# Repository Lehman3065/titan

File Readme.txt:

https://Lehman3065@bitbucket.org/Lehman3065/titan.git
password: lermontov

https://github.com/Lehman3065/titan.git
password: git9....9

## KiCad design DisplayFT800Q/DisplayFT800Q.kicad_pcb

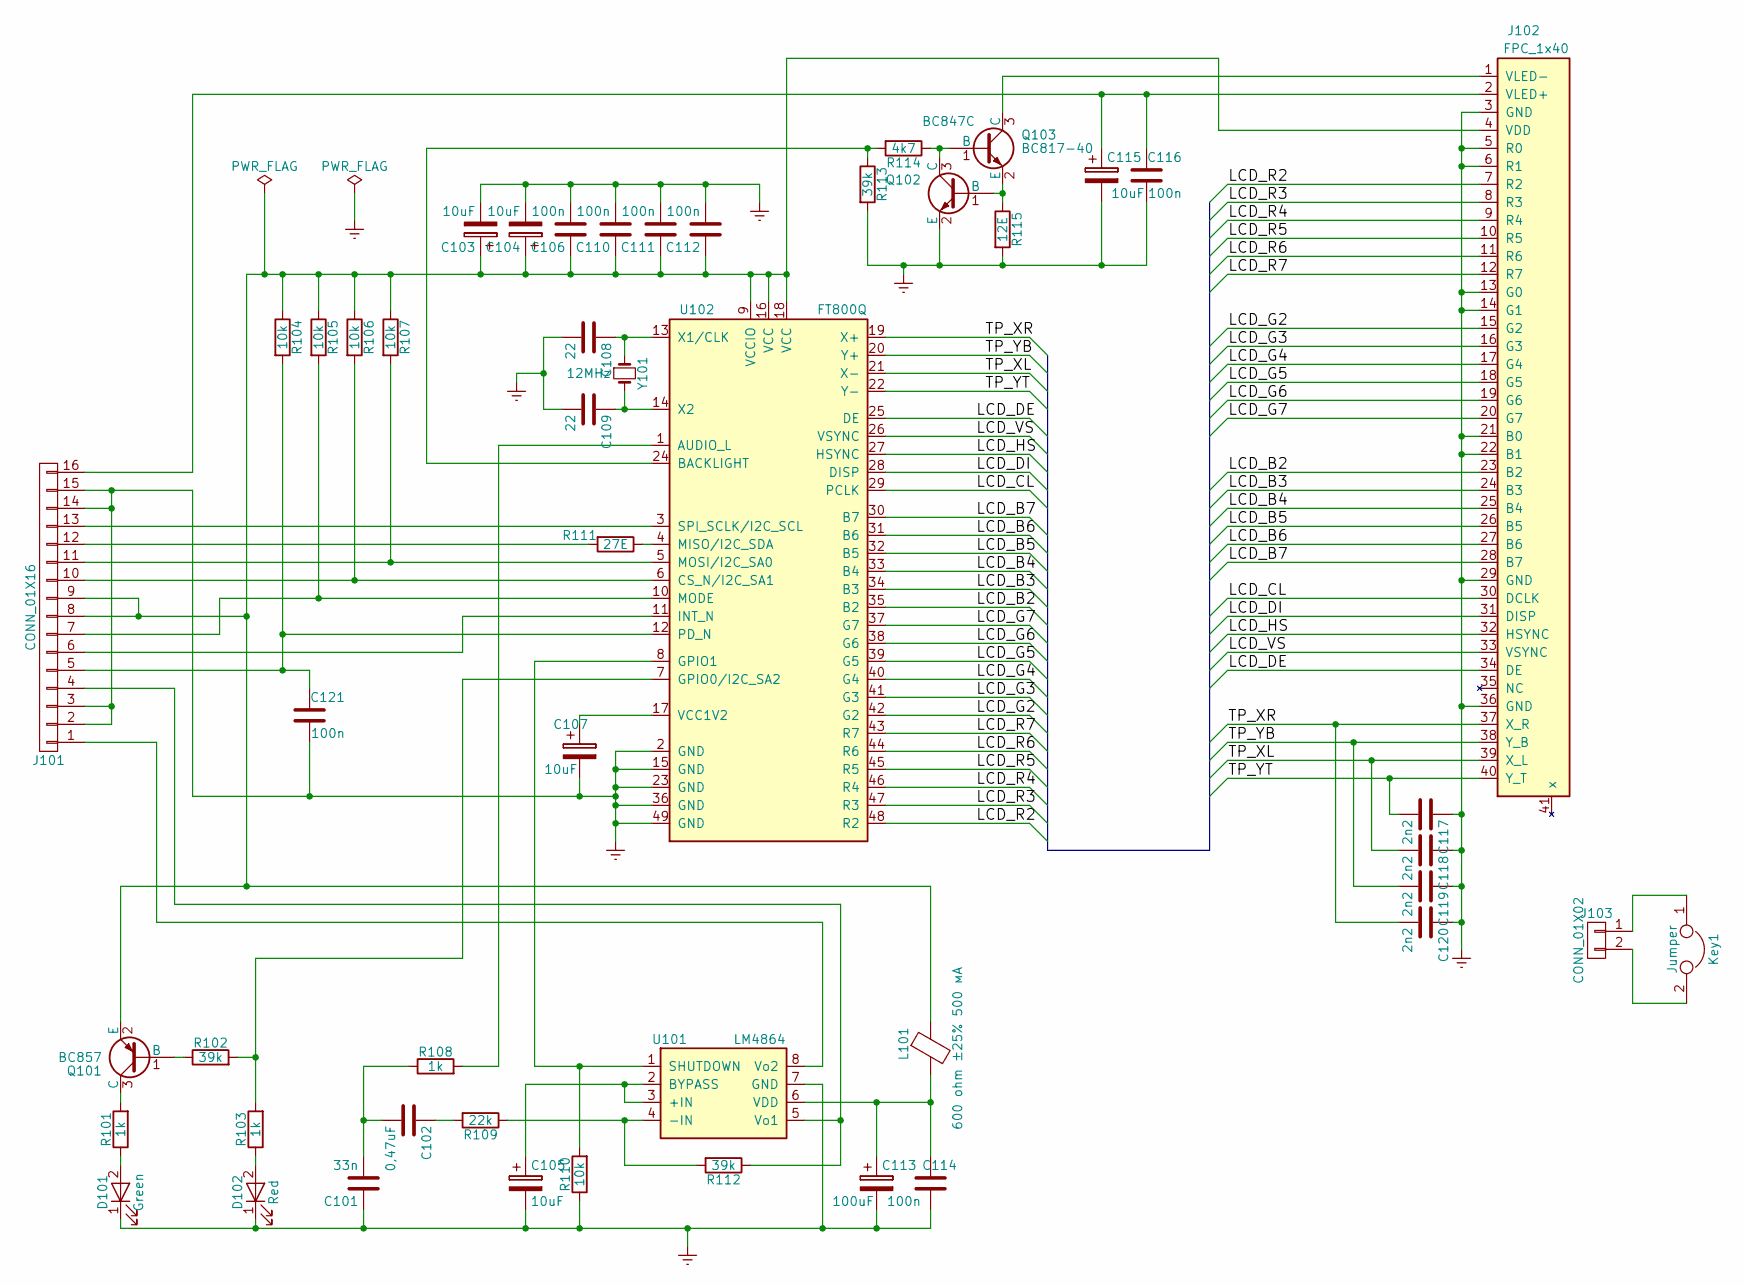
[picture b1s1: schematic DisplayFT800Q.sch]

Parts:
C101: 33n; C_0603
C102: 0,47uF; R_0805
C103, C104, C105, C107, C115: 10uF; C_0805
C106, C110, C111, C112, C114, C116, C121: 100n; C_0603
C108, C109: 22; C_0603
C113: 100uF; CP_Radial_D6.3mm_P2.50mm
C117, C118, C119, C120: 2n2; C_0603
D101: Green; LED_D3.0mm
D102: Red; LED_D3.0mm
J101: CONN_01X16; IDC_DIP_Header_Straight_16pins
J102: FPC_1x40; FPC_1x40_0.5mm
J103: CONN_01X02; TerminalBlock_Pheonix_MKDS1.5-2pol
Key1: Jumper; SW_Tactile_Straight_KSL0Axx1LFTR
L101: 600 ohm ±25% 500 мА; L_0603
Q101: BC857; SOT-23
Q102: BC847C; SOT-23
Q103: BC817-40; SOT-23
R101, R103, R108: 1k; R_0603
R102, R112, R113: 39k; R_0603
R104, R105, R106, R107, R110: 10k; R_0603
R109: 22k; R_0603
R111: 27E; R_0603
R114: 4k7; R_0603
R115: 12E; R_0603
U101: LM4864; TSSOP-8_3x3mm_Pitch0.65mm
U102: FT800Q; QFN-48-1EP_7x7mm_Pitch0.5mm
Y101: 12MHz; Crystal_SMD_HC49-SD

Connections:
/LCD_B2: J102.23 (B2), U102.35 (B2)
/LCD_B3: J102.24 (B3), U102.34 (B3)
/LCD_B4: J102.25 (B4), U102.33 (B4)
/LCD_B5: J102.26 (B5), U102.32 (B5)
/LCD_B6: J102.27 (B6), U102.31 (B6)
/LCD_B7: J102.28 (B7), U102.30 (B7)
/LCD_CL: J102.30 (DCLK), U102.29 (PCLK)
/LCD_DE: J102.34 (DE), U102.25 (DE)
/LCD_DI: J102.31 (DISP), U102.28 (DISP)
/LCD_G2: J102.15 (G2), U102.42 (G2)
/LCD_G3: J102.16 (G3), U102.41 (G3)
/LCD_G4: J102.17 (G4), U102.40 (G4)
/LCD_G5: J102.18 (G5), U102.39 (G5)
/LCD_G6: J102.19 (G6), U102.38 (G6)
/LCD_G7: J102.20 (G7), U102.37 (G7)
/LCD_HS: J102.32 (HSYNC), U102.27 (HSYNC)
/LCD_R2: J102.7 (R2), U102.48 (R2)
/LCD_R3: J102.8 (R3), U102.47 (R3)
/LCD_R4: J102.9 (R4), U102.46 (R4)
/LCD_R5: J102.10 (R5), U102.45 (R5)
/LCD_R6: J102.11 (R6), U102.44 (R6)
/LCD_R7: J102.12 (R7), U102.43 (R7)
/LCD_VS: J102.33 (VSYNC), U102.26 (VSYNC)
/TP_XL: C118.2, J102.39 (X_L), U102.21 (X-)
/TP_XR: C120.2, J102.37 (X_R), U102.19 (X+)
/TP_YB: C119.2, J102.38 (Y_B), U102.20 (Y+)
/TP_YT: C117.2, J102.40 (Y_T), U102.22 (Y-)
Earth: C101.1, C103.2, C104.2, C105.2, C106.2, C107.2, C108.2, C109.2, C110.2, C111.2, C112.2, C113.2, C114.1, C115.2, C116.1, C117.1, C118.1, C119.1, C120.1, C121.1, D101.1 (K), D102.1 (K), J101.2, J101.3, J101.14, J101.15, J102.3 (GND), J102.5 (R0), J102.6 (R1), J102.13 (G0), J102.14 (G1), J102.21 (B0), J102.22 (B1), J102.29 (GND), J102.36 (GND), Q102.2 (E), R110.1, R113.2, R115.2, U101.7 (GND), U102.2 (GND), U102.15 (GND), U102.23 (GND), U102.36 (GND), U102.49 (GND)
unnamed: C101.2, C102.2, R108.1
unnamed: C102.1, R109.2
unnamed: C103.1, C104.1, C106.1, C110.1, C111.1, C112.1, J101.8, J101.9, J102.4 (VDD), L101.1, Q101.2 (E), R104.1, R105.1, R106.1, R107.1, U102.9 (VCCIO), U102.16 (VCC), U102.18 (VCC)
unnamed: C105.1, U101.2 (BYPASS), U101.3 (+IN)
unnamed: C107.1, U102.17 (VCC1V2)
unnamed: C108.1, U102.13 (X1/CLK), Y101.1
unnamed: C109.1, U102.14 (X2), Y101.2
unnamed: C113.1, C114.2, L101.2, U101.6 (VDD)
unnamed: C115.1, C116.2, J101.16, J102.2 (VLED+)
unnamed: D101.2 (A), R101.1
unnamed: D102.2 (A), R103.1
unnamed: J101.1, U101.8 (Vo2)
unnamed: J101.4, R112.1, U101.5 (Vo1)
unnamed: C121.2, J101.5, R104.2, U102.12 (PD_N)
unnamed: J101.6, U102.11 (INT_N)
unnamed: J101.7, R105.2, U102.10 (MODE)
unnamed: J101.10, R106.2, U102.6 (CS_N/I2C_SA1)
unnamed: J101.11, R107.2, U102.5 (MOSI/I2C_SA0)
unnamed: J101.12, R111.2
unnamed: J101.13, U102.3 (SPI_SCLK/I2C_SCL)
unnamed: J102.1 (VLED-), Q103.3 (C)
unnamed: J103.1, Key1.1
unnamed: J103.2, Key1.2
unnamed: Q101.1 (B), R102.1
unnamed: Q101.3 (C), R101.2
unnamed: Q102.1 (B), Q103.2 (E), R115.1
unnamed: Q102.3 (C), Q103.1 (B), R114.1
unnamed: R102.2, R103.2, U102.7 (GPIO0/I2C_SA2)
unnamed: R108.2, U102.1 (AUDIO_L)
unnamed: R109.1, R112.2, U101.4 (-IN)
unnamed: R110.2, U101.1 (SHUTDOWN), U102.8 (GPIO1)
unnamed: R111.1, U102.4 (MISO/I2C_SDA)
unnamed: R113.1, R114.2, U102.24 (BACKLIGHT)

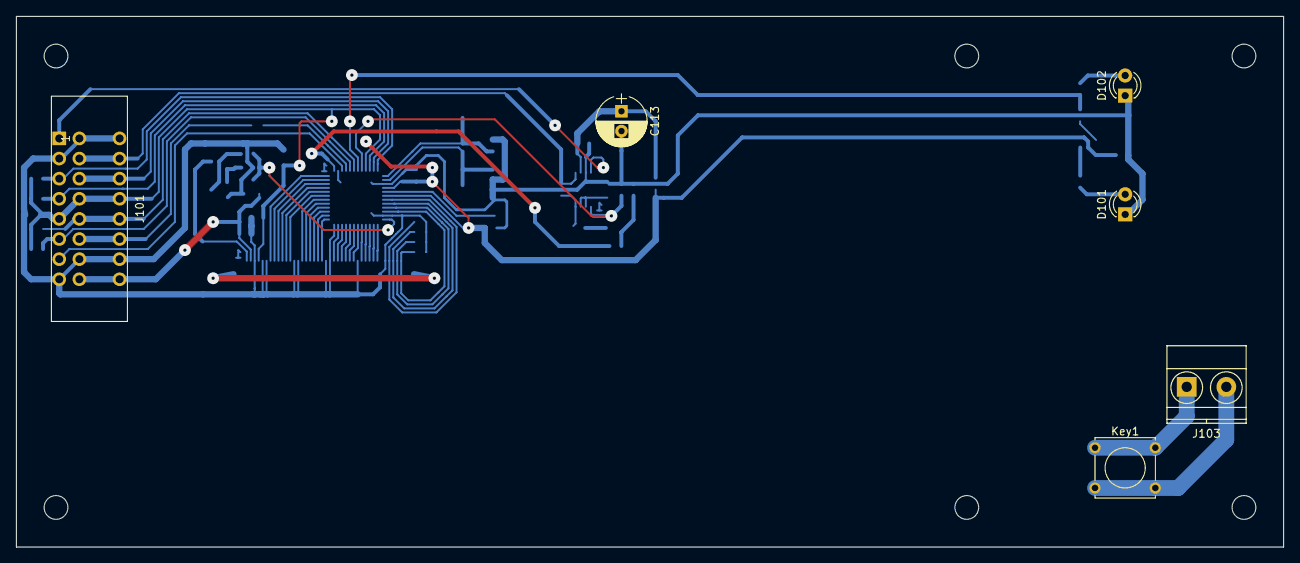
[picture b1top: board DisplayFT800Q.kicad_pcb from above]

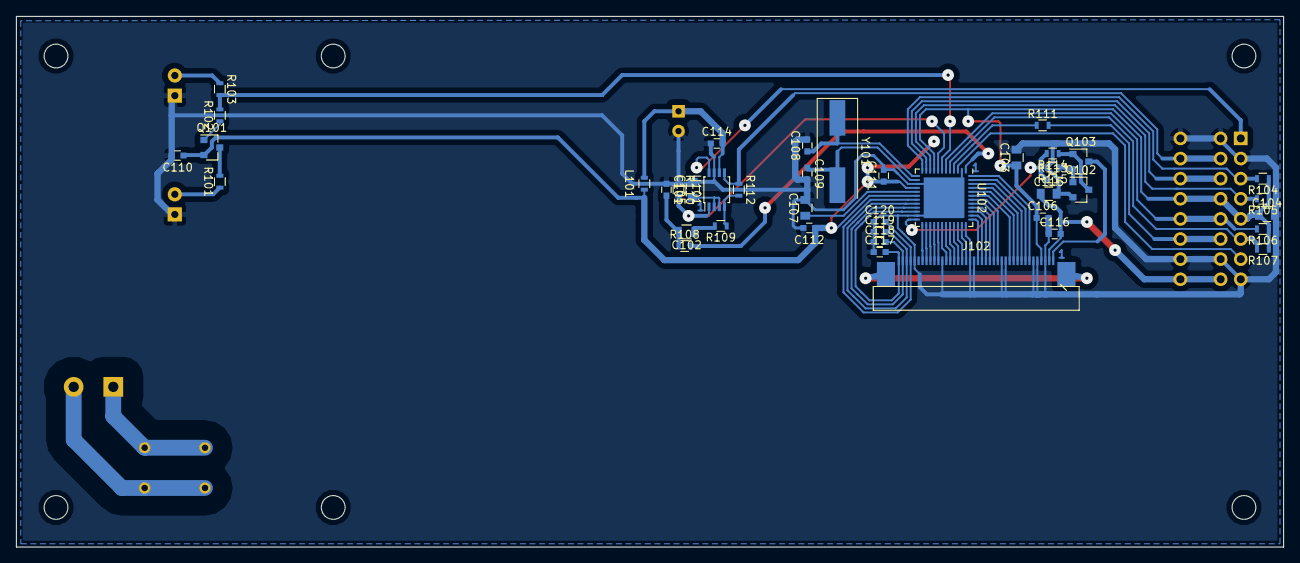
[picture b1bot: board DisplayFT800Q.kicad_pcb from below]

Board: 2 copper layers, 160.0 x 67.0 mm, 48 parts (42 on the bottom side), 61 nets.

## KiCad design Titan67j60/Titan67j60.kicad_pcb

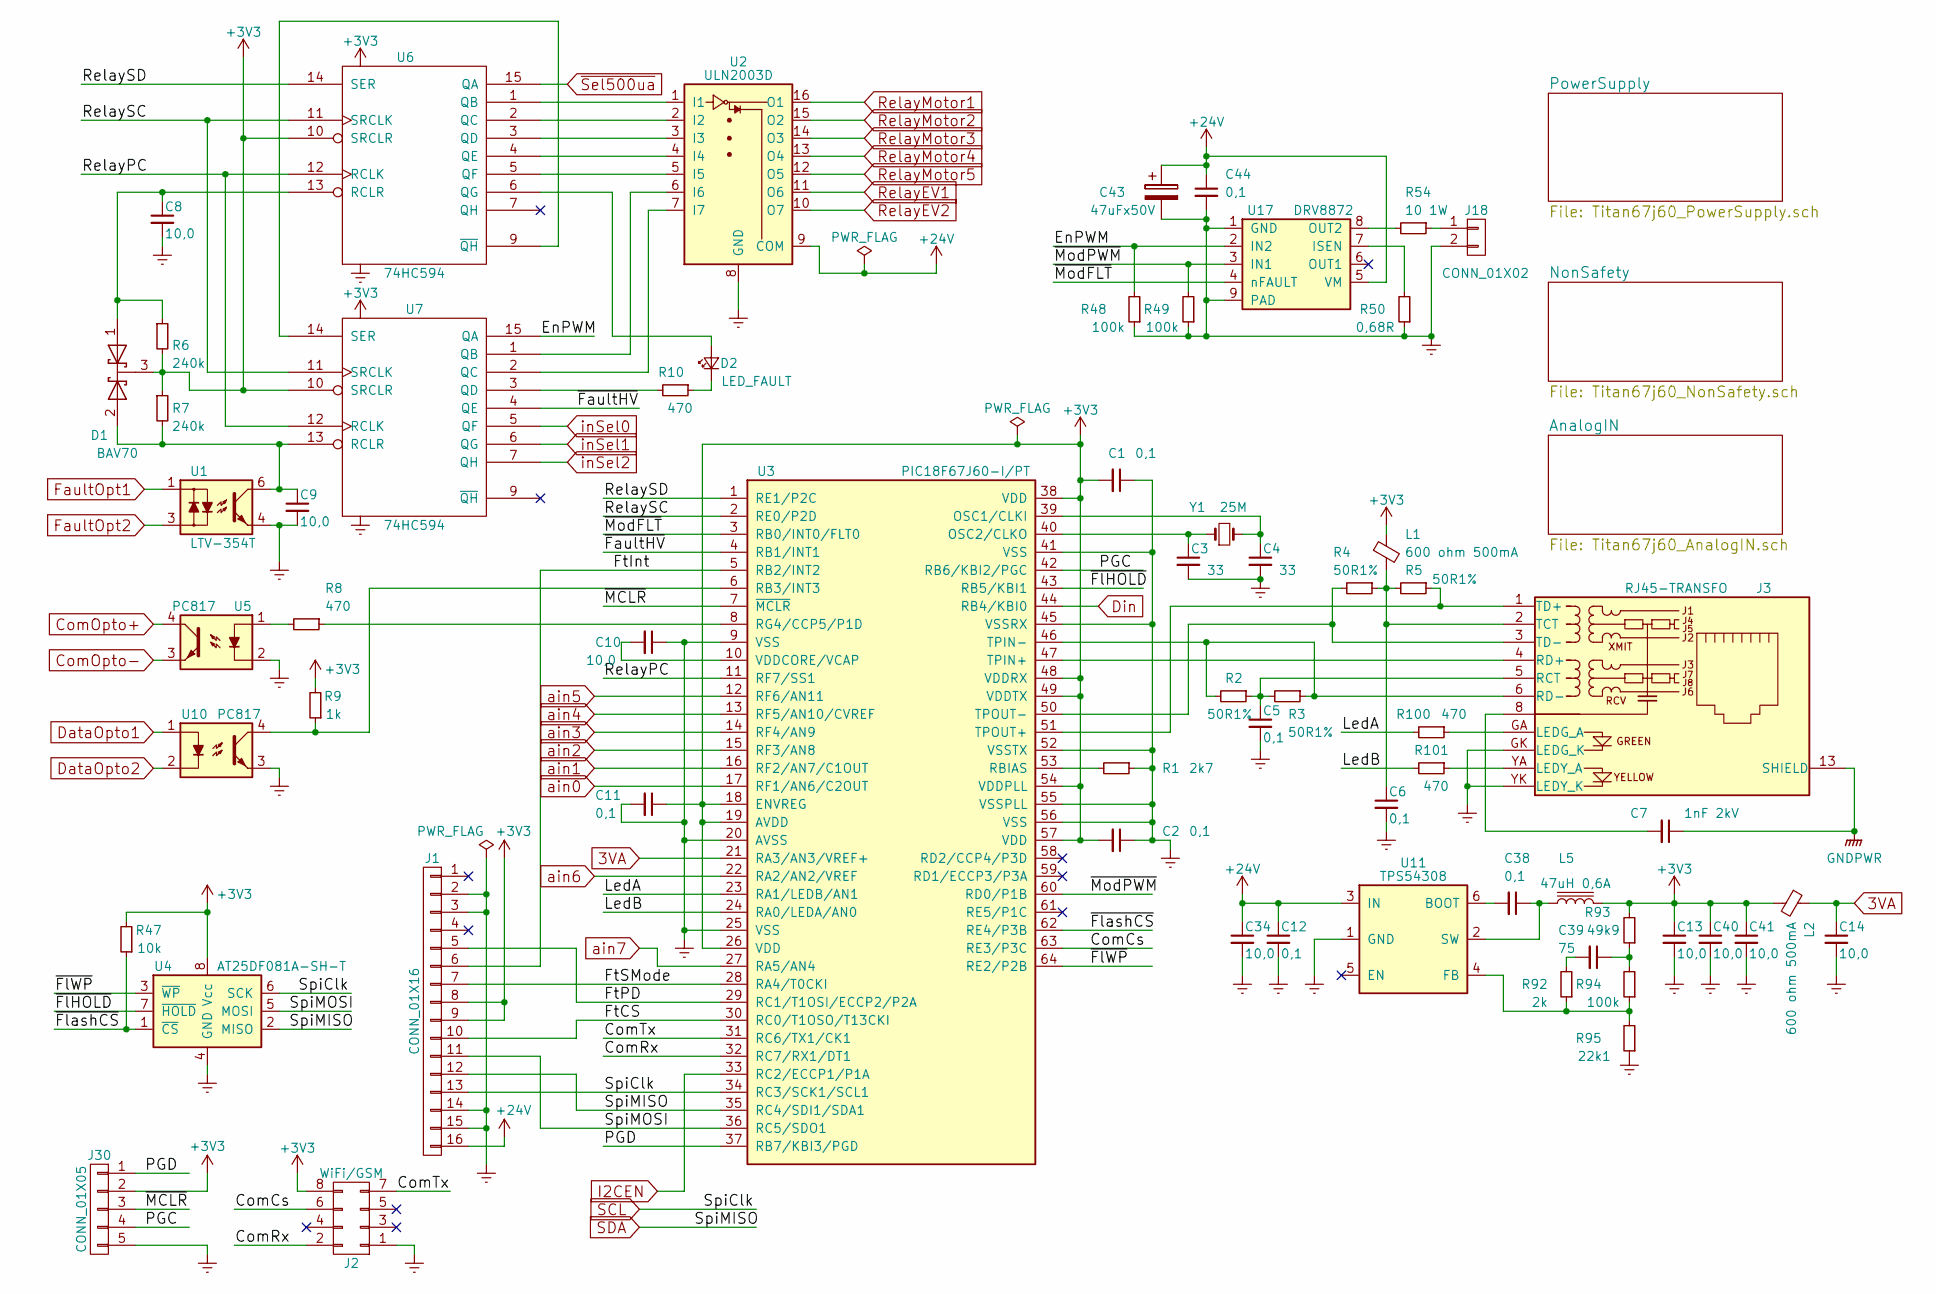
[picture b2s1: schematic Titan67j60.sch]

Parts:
C1, C2, C5, C6, C11, C38, C44: 0,1; C_0603
C3, C4: 33; C_0603
C7: 1nF 2kV; C_Disc_D10.5mm_W5.0mm_P10.00mm
C8, C9, C10, C13, C14, C40, C41: 10,0; C_0805
C12: 0,1; C_0805
C34: 10,0; C_1206
C39: 75; C_0603
C43: 47uFx50V; CP_Radial_D10.0mm_P5.00mm
D1: BAV70; SOT-23
D2: LED_FAULT; LED_D5.0mm
J1: CONN_01X16; Multicomp_MC9A12-1634_2x08x2.54mm_Straight
J2: WiFi/GSM; SDL-108-X-XX_2x04
J3: RJ45-TRANSFO; RJ45_TRANS_J0011D21BNL
J18: CONN_01X02; PhoenixContact_MSTBVA-G_02x5.08mm_Vertical
J30: CONN_01X05; TerminalBlock_Pheonix_MPT-2.54mm_5pol
L1, L2: 600 ohm 500mA; L_0603
L5: 47uH 0,6A; L_Vishay_IHLP-5050
R1: 2k7; R_0603
R2, R3, R4, R5: 50R1%; R_0603
R6, R7: 240k; R_0603
R8, R10, R100, R101: 470; R_0603
R9: 1k; R_0603
R47: 10k; R_0805
R48, R49, R94: 100k; R_0603
R50: 0,68R; R_1210
R54: 10 1W; R_Axial_DIN0414_L11.9mm_D4.5mm_P15.24mm_Horizontal
R92: 2k; R_0603
R93: 49k9; R_0603
R95: 22k1; R_0603
U1: LTV-354T; DIP-6_W7.62mm_SMD
U2: ULN2003D; SOIC-16_3.9x9.9mm_Pitch1.27mm
U3: PIC18F67J60-I/PT; TQFP-64_10x10mm_Pitch0.5mm
U4: AT25DF081A-SH-T; SOIC-8_3.9x4.9mm_Pitch1.27mm
U5, U10: PC817; DIP-4_W7.62mm
U6, U7: 74HC594; SOIC-16_3.9x9.9mm_Pitch1.27mm
U11: TPS54308; SOT-23-6
U17: DRV8872; TI_SO-PowerPAD-8
Y1: 25M; Crystal_SMD_HC49-SD

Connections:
3VA: C14.1, L2.1, U3.21 (RA3/AN3/VREF+); also elsewhere on the board
+3V3: C1.2, C2.2, C11.1, C13.1, C40.1, C41.1, D1.3 (K), J1.8, J1.9, J2.8, J30.2, L1.1, L2.2, L5.2, R6.2, R7.1, R9.2, R47.2, R93.2, U3.18 (ENVREG), U3.19 (AVDD), U3.26 (VDD), U3.38 (VDD), U3.48 (VDDRX), U3.49 (VDDTX), U3.54 (VDDPLL), U3.57 (VDD), U4.8 (Vcc), U6.10 (SRCLR), U6.16 (VCC), U7.10 (SRCLR), U7.16 (VCC); also elsewhere on the board
+24V: C12.1, C34.1, C43.1, C44.1, J1.16, U2.9 (COM), U11.3 (IN), U17.5 (VM); also elsewhere on the board
/ComCs: J2.6, U3.63 (RE3/P3C)
/ComRx: J2.2, U3.32 (RC7/RX1/DT1)
/ComTx: J2.7, U3.31 (RC6/TX1/CK1)
/EnPWM: R48.2, U7.15 (QA), U17.2 (IN2)
/FtCS: J1.10, U3.30 (RC0/T1OSO/T13CKI)
/FtInt: J1.6, U3.5 (RB2/INT2)
/FtPD: J1.5, U3.29 (RC1/T1OSI/ECCP2/P2A)
/FtSMode: J1.7, U3.28 (RA4/T0CKI)
/LedA: R100.2, U3.23 (RA1/LEDB/AN1)
/LedB: R101.2, U3.24 (RA0/LEDA/AN0)
/PGC: J30.4, U3.42 (RB6/KBI2/PGC)
/PGD: J30.1, U3.37 (RB7/KBI3/PGD)
/RelayPC: U3.11 (RF7/SS1), U6.12 (RCLK), U7.12 (RCLK)
/RelaySC: U3.2 (RE0/P2D), U6.11 (SRCLK), U7.11 (SRCLK)
/RelaySD: U3.1 (RE1/P2C), U6.14 (SER)
/SpiMOSI: J1.11, U3.36 (RC5/SDO1), U4.5 (MOSI)
/~FaultHV: U3.4 (RB1/INT1), U7.4 (QE)
/~FlHOLD: U3.43 (RB5/KBI1), U4.7 (~HOLD)
/~FlWP: U3.64 (RE2/P2B), U4.3 (~WP)
/~FlashCS: R47.1, U3.62 (RE4/P3B), U4.1 (~CS)
/~MCLR: J30.3, U3.7 (~MCLR)
/~ModFLT: U3.3 (RB0/INT0/FLT0), U17.4 (nFAULT)
/~ModPWM: R49.2, U3.60 (RD0/P1B), U17.3 (IN1)
ComOpto-: U5.3, U10.2; also elsewhere on the board
DataOpto1: U10.1; also elsewhere on the board
Din: U3.44 (RB4/KBI0); also elsewhere on the board
Earth: C1.1, C2.1, C3.2, C4.2, C5.2, C6.2, C8.2, C9.2, C10.1, C11.2, C12.2, C13.2, C14.2, C34.2, C40.2, C41.2, C43.2, C44.2, J1.2, J1.3, J1.14, J1.15, J2.1, J3.GK (LEDG_K), J3.YK (LEDY_K), J18.2, J30.5, R1.1, R48.1, R49.1, R50.1, R95.1, U1.4, U2.8 (GND), U3.9 (VSS), U3.20 (AVSS), U3.25 (VSS), U3.41 (VSS), U3.45 (VSSRX), U3.52 (VSSTX), U3.55 (VSSPLL), U3.56 (VSS), U4.4 (GND), U5.2, U6.8 (GND), U7.8 (GND), U10.3, U11.1 (GND), U17.1 (GND), U17.9 (PAD); also elsewhere on the board
FaultOpt1: U1.1; also elsewhere on the board
FaultOpt2: U1.3; also elsewhere on the board
GNDPWR: C7.1, J3.13 (SHIELD); also elsewhere on the board
I2CEN: U3.33 (RC2/ECCP1/P1A); also elsewhere on the board
unnamed: C3.1, U3.40 (OSC2/CLKO), Y1.1
unnamed: C4.1, U3.39 (OSC1/CLKI), Y1.2
unnamed: C5.1, J3.5 (RCT), R2.1, R3.2
unnamed: C6.1, J3.2 (TCT), L1.2, R4.1, R5.2
unnamed: C7.2, J3.8
unnamed: C8.1, D1.1 (A), R6.1, U6.13 (RCLR)
unnamed: C9.1, D1.2 (A), R7.2, U1.6, U7.13 (RCLR)
unnamed: C10.2, U3.10 (VDDCORE/VCAP)
unnamed: C38.1, L5.1, U11.2 (SW)
unnamed: C38.2, U11.6 (BOOT)
unnamed: C39.1, R93.1, R94.2
unnamed: C39.2, R92.2
unnamed: D2.1 (K), R10.1
unnamed: D2.2 (A), U6.6 (QG)
unnamed: J3.1 (TD+), R5.1, U3.51 (TPOUT+)
unnamed: J3.3 (TD-), R4.2, U3.50 (TPOUT-)
unnamed: J3.4 (RD+), U3.47 (TPIN+)
unnamed: J3.6 (RD-), R2.2, R3.1, U3.46 (TPIN-)
unnamed: J3.GA (LEDG_A), R100.1
unnamed: J3.YA (LEDY_A), R101.1
unnamed: J18.1, R54.1
unnamed: R1.2, U3.53 (RBIAS)
unnamed: R8.1, U3.8 (RG4/CCP5/P1D)
unnamed: R8.2, U5.1
unnamed: R9.1, U3.6 (RB3/INT3), U10.4
unnamed: R10.2, U7.3 (QD)
unnamed: R50.2, U17.7 (ISEN)
unnamed: R54.2, U17.8 (OUT2)
unnamed: R92.1, R94.1, R95.2, U11.4 (FB)
unnamed: U2.1 (I1), U6.1 (QB)
unnamed: U2.2 (I2), U6.2 (QC)
unnamed: U2.3 (I3), U6.3 (QD)
unnamed: U2.4 (I4), U6.4 (QE)
unnamed: U2.5 (I5), U6.5 (QF)
unnamed: U2.6 (I6), U7.1 (QB)
unnamed: U2.7 (I7), U7.2 (QC)
unnamed: U6.9 (~QH), U7.14 (SER)
RelayEV1: U2.11 (O6); also elsewhere on the board
RelayEV2: U2.10 (O7); also elsewhere on the board
RelayMotor1: U2.16 (O1); also elsewhere on the board
RelayMotor2: U2.15 (O2); also elsewhere on the board
RelayMotor3: U2.14 (O3); also elsewhere on the board
RelayMotor4: U2.13 (O4); also elsewhere on the board
RelayMotor5: U2.12 (O5); also elsewhere on the board
SCL: J1.13, U3.34 (RC3/SCK1/SCL1), U4.6 (SCK); also elsewhere on the board
SDA: J1.12, U3.35 (RC4/SDI1/SDA1), U4.2 (MISO); also elsewhere on the board
ain0: U3.17 (RF1/AN6/C2OUT); also elsewhere on the board
ain1: U3.16 (RF2/AN7/C1OUT); also elsewhere on the board
ain2: U3.15 (RF3/AN8); also elsewhere on the board
ain3: U3.14 (RF4/AN9); also elsewhere on the board
ain4: U3.13 (RF5/AN10/CVREF); also elsewhere on the board
ain5: U3.12 (RF6/AN11); also elsewhere on the board
ain6: U3.22 (RA2/AN2/VREF); also elsewhere on the board
ain7: U3.27 (RA5/AN4); also elsewhere on the board
inSel0: U7.5 (QF); also elsewhere on the board
inSel1: U7.6 (QG); also elsewhere on the board
inSel2: U7.7 (QH); also elsewhere on the board
~Sel500ua: U6.15 (QA); also elsewhere on the board

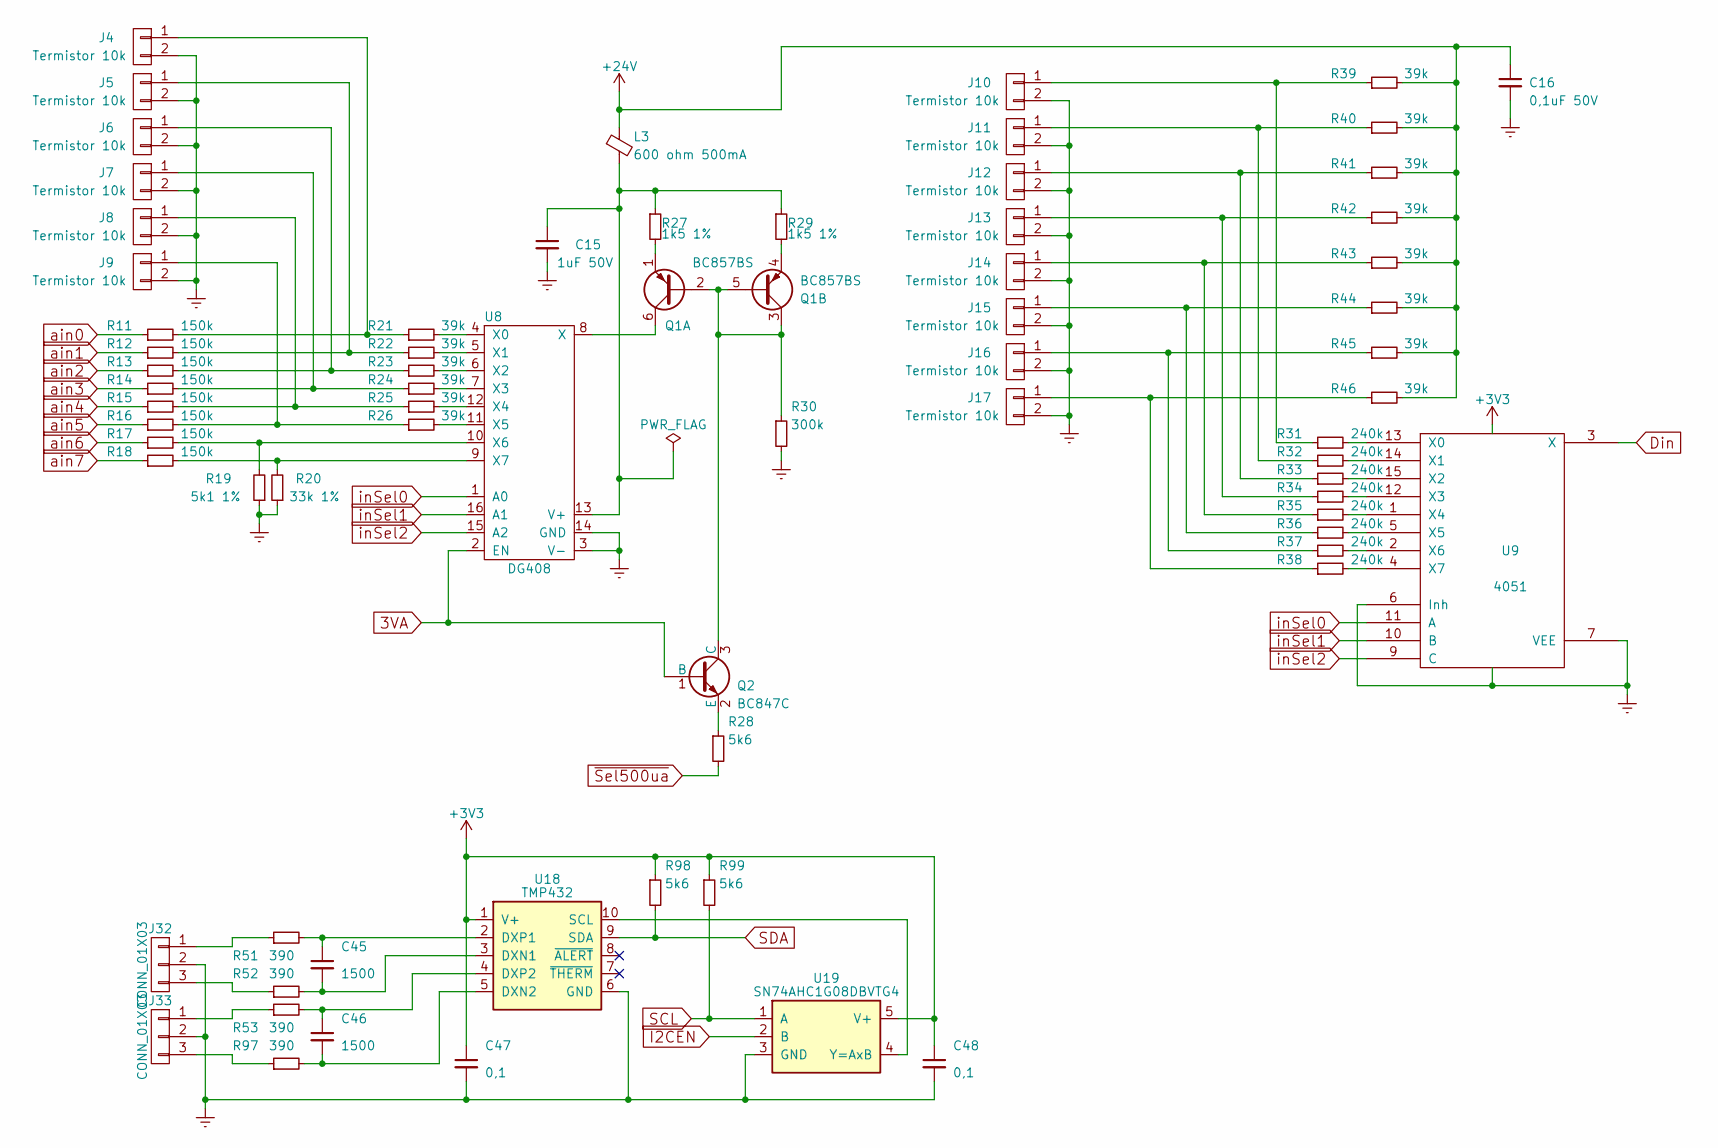
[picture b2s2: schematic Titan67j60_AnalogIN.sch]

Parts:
C15: 1uF 50V; C_1206
C16: 0,1uF 50V; C_0805
C45, C46: 1500; C_0603
C47, C48: 0,1; C_0603
J4, J5, J6, J7, J8, J9: Termistor 10k; PhoenixContact_MC-G_02x3.81mm_Angled
J10, J11, J12, J13, J14, J15, J16, J17: Termistor 10k; PhoenixContact_MC-G_02x5.08mm_Angled
J32, J33: CONN_01X03; TerminalBlock_Pheonix_MKDS1.5-3pol
L3: 600 ohm 500mA; L_0603
Q1: BC857BS; SOT-363_SC-70-6
Q2: BC847C; SOT-23
R11, R12, R13, R14, R15, R16, R17, R18: 150k; R_0805
R19: 5k1 1%; R_0805
R20: 33k 1%; R_0805
R21, R22, R23, R24, R25, R26, R39, R40, R41, R42, R43, R44, R45, R46: 39k; R_0805
R27, R29: 1k5 1%; R_0603
R28, R98, R99: 5k6; R_0603
R30: 300k; R_0603
R31, R32, R33, R34, R35, R36, R37, R38: 240k; R_0805
R51, R52, R53, R97: 390; R_0805
U8: DG408; SOIC-16_3.9x9.9mm_Pitch1.27mm
U9: 4051; SOIC-16_3.9x9.9mm_Pitch1.27mm
U18: TMP432; MSOP-10_3x3mm_Pitch0.5mm
U19: SN74AHC1G08DBVTG4; SOT-23-5

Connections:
3VA: Q2.1 (B), U8.2 (EN); also elsewhere on the board
+3V3: C47.1, C48.1, R98.1, R99.1, U9.16 (VDD), U18.1 (V+), U19.5 (V+); also elsewhere on the board
+24V: C16.1, L3.1, R39.2, R40.2, R41.2, R42.2, R43.2, R44.2, R45.2, R46.2; also elsewhere on the board
Din: U9.3 (X); also elsewhere on the board
Earth: C15.2, C16.2, C47.2, C48.2, J4.2, J5.2, J6.2, J7.2, J8.2, J9.2, J10.2, J11.2, J12.2, J13.2, J14.2, J15.2, J16.2, J17.2, J32.2, J33.2, R19.1, R20.1, R30.2, U8.3 (V-), U8.14 (GND), U9.6 (Inh), U9.7 (VEE), U9.8 (VSS), U18.6 (GND), U19.3 (GND); also elsewhere on the board
I2CEN: U19.2 (B); also elsewhere on the board
unnamed: C15.1, L3.2, R27.1, R29.1, U8.13 (V+)
unnamed: C45.1, R51.2, U18.2 (DXP1)
unnamed: C45.2, R52.2, U18.3 (DXN1)
unnamed: C46.1, R53.2, U18.4 (DXP2)
unnamed: C46.2, R97.2, U18.5 (DXN2)
unnamed: J4.1, R11.2, R21.1
unnamed: J5.1, R12.2, R22.1
unnamed: J6.1, R13.2, R23.1
unnamed: J7.1, R14.2, R24.1
unnamed: J8.1, R15.2, R25.1
unnamed: J9.1, R16.2, R26.1
unnamed: J10.1, R31.1, R39.1
unnamed: J11.1, R32.1, R40.1
unnamed: J12.1, R33.1, R41.1
unnamed: J13.1, R34.1, R42.1
unnamed: J14.1, R35.1, R43.1
unnamed: J15.1, R36.1, R44.1
unnamed: J16.1, R37.1, R45.1
unnamed: J17.1, R38.1, R46.1
unnamed: J32.1, R51.1
unnamed: J32.3, R52.1
unnamed: J33.1, R53.1
unnamed: J33.3, R97.1
unnamed: Q1.1 (E1), R27.2
unnamed: Q1.2 (B1), Q1.3 (C2), Q1.5 (B2), Q2.3 (C), R30.1
unnamed: Q1.4 (E2), R29.2
unnamed: Q1.6 (C1), U8.8 (X)
unnamed: Q2.2 (E), R28.1
unnamed: R17.2, R19.2, U8.10 (X6)
unnamed: R18.2, R20.2, U8.9 (X7)
unnamed: R21.2, U8.4 (X0)
unnamed: R22.2, U8.5 (X1)
unnamed: R23.2, U8.6 (X2)
unnamed: R24.2, U8.7 (X3)
unnamed: R25.2, U8.12 (X4)
unnamed: R26.2, U8.11 (X5)
unnamed: R31.2, U9.13 (X0)
unnamed: R32.2, U9.14 (X1)
unnamed: R33.2, U9.15 (X2)
unnamed: R34.2, U9.12 (X3)
unnamed: R35.2, U9.1 (X4)
unnamed: R36.2, U9.5 (X5)
unnamed: R37.2, U9.2 (X6)
unnamed: R38.2, U9.4 (X7)
unnamed: U18.10 (SCL), U19.4 (Y=AxB)
SCL: R99.2, U19.1 (A); also elsewhere on the board
SDA: R98.2, U18.9 (SDA); also elsewhere on the board
ain0: R11.1; also elsewhere on the board
ain1: R12.1; also elsewhere on the board
ain2: R13.1; also elsewhere on the board
ain3: R14.1; also elsewhere on the board
ain4: R15.1; also elsewhere on the board
ain5: R16.1; also elsewhere on the board
ain6: R17.1; also elsewhere on the board
ain7: R18.1; also elsewhere on the board
inSel0: U8.1 (A0), U9.11 (A); also elsewhere on the board
inSel1: U8.16 (A1), U9.10 (B); also elsewhere on the board
inSel2: U8.15 (A2), U9.9 (C); also elsewhere on the board
~Sel500ua: R28.2; also elsewhere on the board

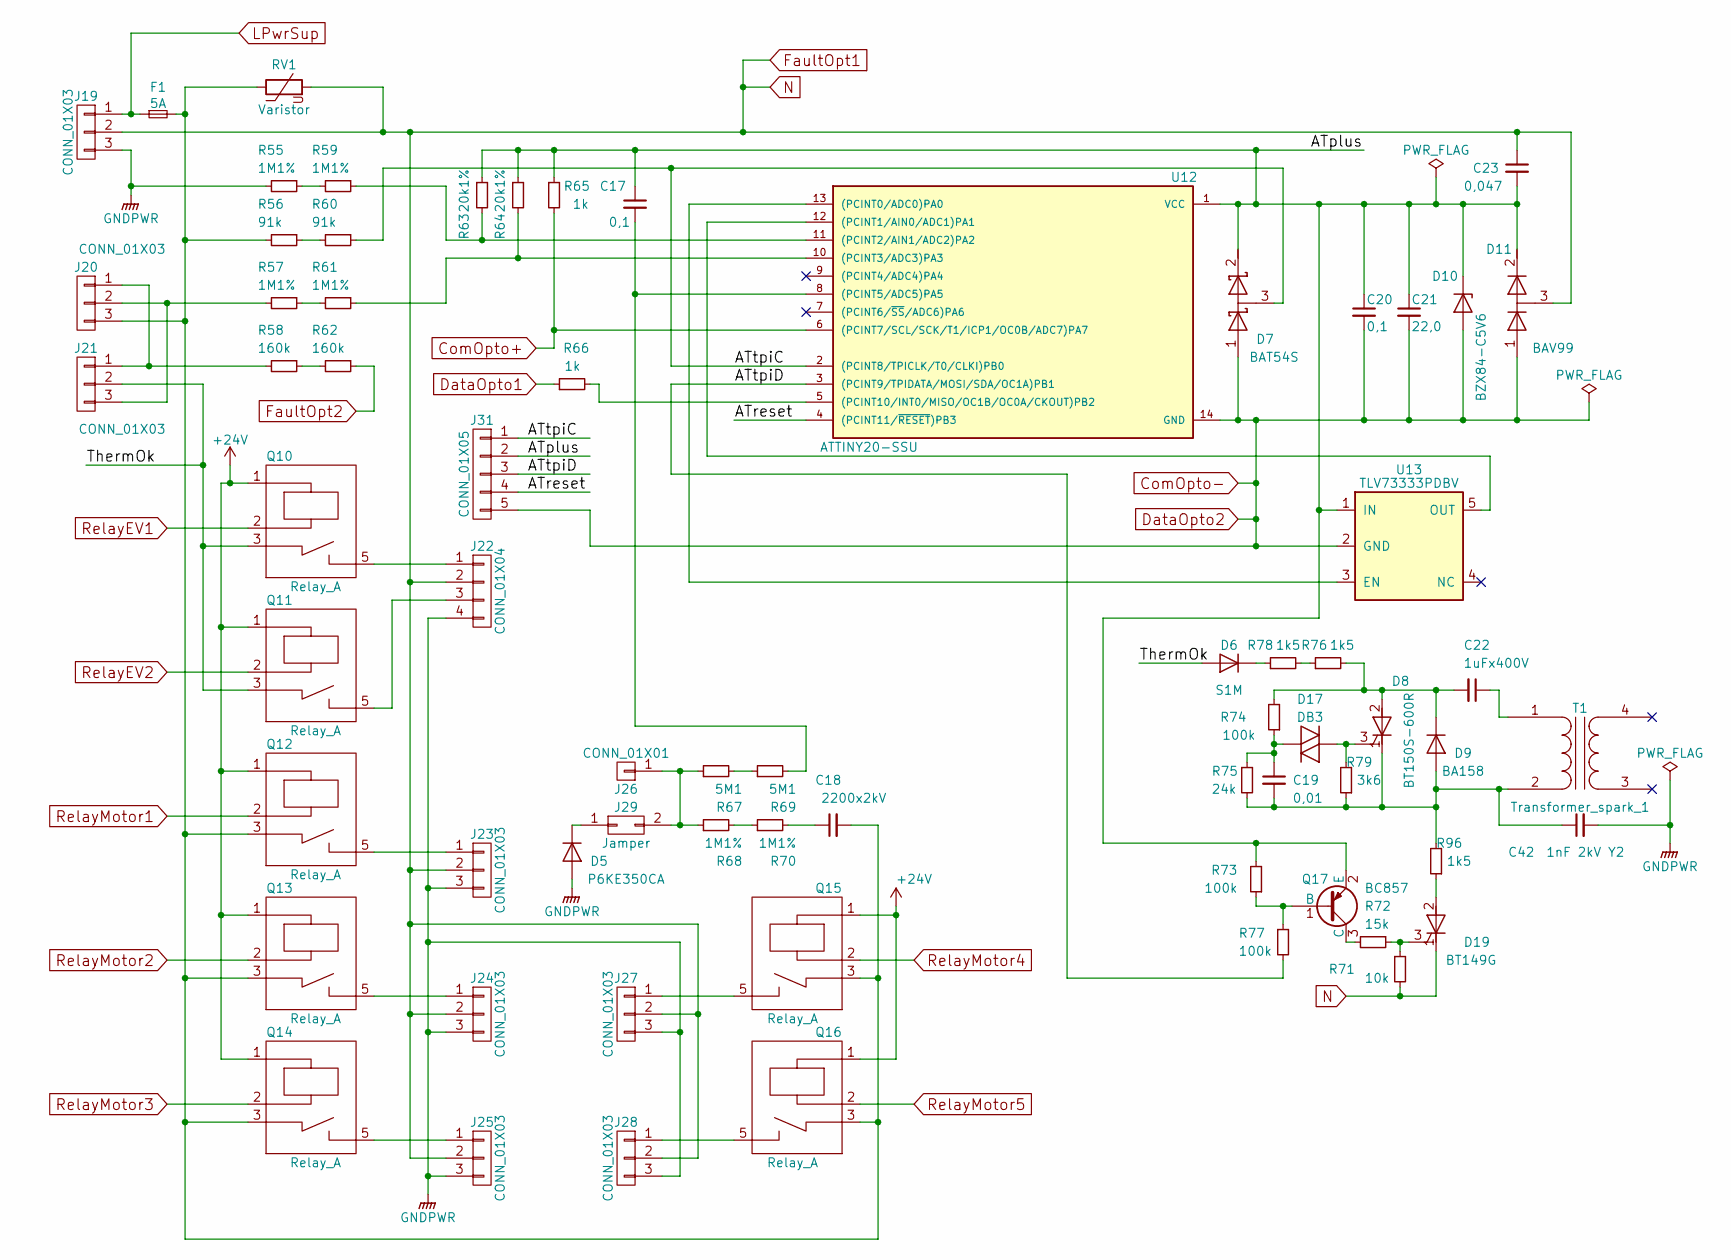
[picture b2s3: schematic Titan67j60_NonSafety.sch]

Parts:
C17, C20: 0,1; C_0603
C18: 2200x2kV; C_Disc_D10.5mm_W5.0mm_P10.00mm
C19: 0,01; C_0603
C21: 22,0; C_0805
C22: 1uFx400V; C_Rect_L24.0mm_W10.1mm_P22.50mm_MKT
C23: 0,047; C_0603
C42: 1nF 2kV Y2; C_Disc_D10.5mm_W5.0mm_P10.00mm
D5: P6KE350CA; D_DO-15_P12.70mm_Horizontal
D6: S1M; D_DO-41_SOD81_P10.16mm_Horizontal
D7: BAT54S; SOT-23
D8: BT150S-600R; TO-252-3_TabPin2
D9: BA158; D_DO-41_SOD81_P10.16mm_Horizontal
D10: BZX84-C5V6; D_SOT-23_ANK
D11: BAV99; SOT-23
D17: DB3; D_DO-35_SOD27_P10.16mm_Horizontal
D19: BT149G; TO-92_Molded_Wide_Oval_Reverse
F1: 5A; Fuseholder5x20_horiz_open_inline_Type-I
J19, J20, J21: CONN_01X03; PhoenixContact_MSTBVA-G_03x5.08mm_Vertical
J22: CONN_01X04; Connector_04x3.96mm
J23, J24, J25, J27, J28: CONN_01X03; Connector_03x3.96mm
J26: CONN_01X01; 1pin
J29: Jamper; Molex_KK-6410-02_02x2.54mm_Straight
J31: CONN_01X05; Molex_KK-6410-05_05x2.54mm_Straight
Q10, Q11, Q12, Q13, Q14, Q15, Q16: Relay_A; TRD_A
Q17: BC857; SOT-23
R55, R57, R59, R61, R68, R70: 1M1%; R_1206
R56, R60: 91k; R_1206
R58, R62: 160k; R_1206
R63, R64: 20k1%; R_0603
R65, R66: 1k; R_0603
R67, R69: 5M1; R_1206
R71: 10k; R_0603
R72: 15k; R_0603
R73, R77: 100k; R_0603
R74: 100k; R_1206
R75: 24k; R_0805
R76, R78, R96: 1k5; R_1206
R79: 3k6; R_0603
RV1: Varistor
T1: Transformer_spark_1
U12: ATTINY20-SSU; SOIC-14_3.9x8.7mm_Pitch1.27mm
U13: TLV73333PDBV; SOT-23-5

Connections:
+24V: Q10.1, Q11.1, Q12.1, Q13.1, Q14.1, Q15.1, Q16.1; also elsewhere on the board
/NonSafety/ATreset: J31.4, U12.4 ((PCINT11/~RESET~)PB3)
/NonSafety/ATtpiC: D7.3 (common), J31.1, R60.1, U12.2 ((PCINT8/TPICLK/T0/CLKI)PB0)
/NonSafety/ATtpiD: J31.3, R77.2, U12.3 ((PCINT9/TPIDATA/MOSI/SDA/OC1A)PB1)
/NonSafety/ThermOk: D6.2 (A), J21.2, Q10.3, Q11.3
ComOpto-: C20.2, C21.2, D7.1 (A), D10.2 (A), D11.1 (A), J31.5, U12.14 (GND), U13.2 (GND); also elsewhere on the board
DataOpto1: R66.1; also elsewhere on the board
FaultOpt1: C23.1, D11.3 (common), D19.1 (K), J19.2, J22.2, J23.2, J24.2, J25.2, J27.2, J28.2, R71.2, RV1.2; also elsewhere on the board
FaultOpt2: R62.1; also elsewhere on the board
GNDPWR: C42.2, D5.2 (A), J19.3, J22.4, J23.3, J24.3, J25.3, J27.3, J28.3, R55.2; also elsewhere on the board
LPwrSup: F1.1, J19.1; also elsewhere on the board
unnamed: C17.2, R69.2, U12.8 ((PCINT5/ADC5)PA5)
unnamed: C18.1, R70.2
unnamed: C18.2, F1.2, J20.3, Q12.3, Q13.3, Q14.3, Q15.3, Q16.3, R56.2, RV1.1
unnamed: C19.1, D17.2 (A), R74.1, R75.1
unnamed: C19.2, C42.1, D8.1 (K), D9.2 (A), R75.2, R79.1, R96.2, T1.2 (AB)
unnamed: C22.1, T1.1 (AA)
unnamed: C22.2, D8.2 (A), D9.1 (K), R74.2, R76.2
unnamed: D5.1 (K), J29.1
unnamed: D6.1 (K), R78.1
unnamed: D8.3 (G), D17.1 (K), R79.2
unnamed: D19.2 (A), R96.1
unnamed: D19.3 (G), R71.1, R72.1
unnamed: J20.1, J21.1, R58.2
unnamed: J20.2, J21.3, R57.2
unnamed: J22.1, Q10.5
unnamed: J22.3, Q11.5
unnamed: J23.1, Q12.5
unnamed: J24.1, Q13.5
unnamed: J25.1, Q14.5
unnamed: J26.1, J29.2, R67.1, R68.1
unnamed: J27.1, Q15.5
unnamed: J28.1, Q16.5
unnamed: Q17.1 (B), R73.1, R77.1
unnamed: Q17.3 (C), R72.2
unnamed: R55.1, R59.2
unnamed: R56.1, R60.2
unnamed: R57.1, R61.2
unnamed: R58.1, R62.2
unnamed: R59.1, R63.2, U12.11 ((PCINT2/AIN1/ADC2)PA2)
unnamed: R61.1, R64.2, U12.10 ((PCINT3/ADC3)PA3)
unnamed: R66.2, U12.5 ((PCINT10/INT0/MISO/OC1B/OC0A/CKOUT)PB2)
unnamed: R67.2, R69.1
unnamed: R68.2, R70.1
unnamed: R76.1, R78.2
unnamed: U12.12 ((PCINT1/AIN0/ADC1)PA1), U13.5 (OUT)
RelayEV1: Q10.2; also elsewhere on the board
RelayEV2: Q11.2; also elsewhere on the board
RelayMotor1: Q12.2; also elsewhere on the board
RelayMotor2: Q13.2; also elsewhere on the board
RelayMotor3: Q14.2; also elsewhere on the board
RelayMotor4: Q15.2; also elsewhere on the board
RelayMotor5: Q16.2; also elsewhere on the board

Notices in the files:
Titan67j60_Soft/FirstProbe/First.X/mcc_generated_files/pin_manager.h:
Copyright (c) 2013 - 2015 released Microchip Technology Inc.  All rights reserved.
